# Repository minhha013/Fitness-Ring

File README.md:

# Smart Fitness Ring PCB

This branch contains the PCB design files for the Smart Fitness Ring project, a low-cost wearable device designed to track basic biometrics such as steps, heart rate, and Basal Metabolic Rate (BMR). The purpose of this branch is to document the electrical design and hardware development process behind the custom ring electronics.

The PCB is being developed to support a compact and wearable form factor while integrating the key sensing and processing components needed for health tracking. Because the ring is intended to remain small, lightweight, and practical, the PCB design requires careful consideration of size constraints, component placement, routing, and power management.

## Purpose

The goal of this PCB design is to create a reliable and compact hardware platform that can serve as the foundation for an affordable fitness ring. Many commercial smart rings are expensive and often require subscription fees, which can make health tracking less accessible. This project aims to explore how a custom-designed solution can provide useful biometric tracking at a lower cost.

## PCB Features

- Custom PCB designed in KiCad
- Intended for integration into a compact smart ring
- Supports step tracking functionality
- Supports heart rate sensing
- Supports BMR estimation through collected biometric data
- Designed with wearable size constraints in mind

## Current Status

PCB design in progress.

## Notes

This branch is dedicated specifically to PCB development and hardware design. Other parts of the project, such as CAD modeling, enclosure design, and software/app development, are managed separately.

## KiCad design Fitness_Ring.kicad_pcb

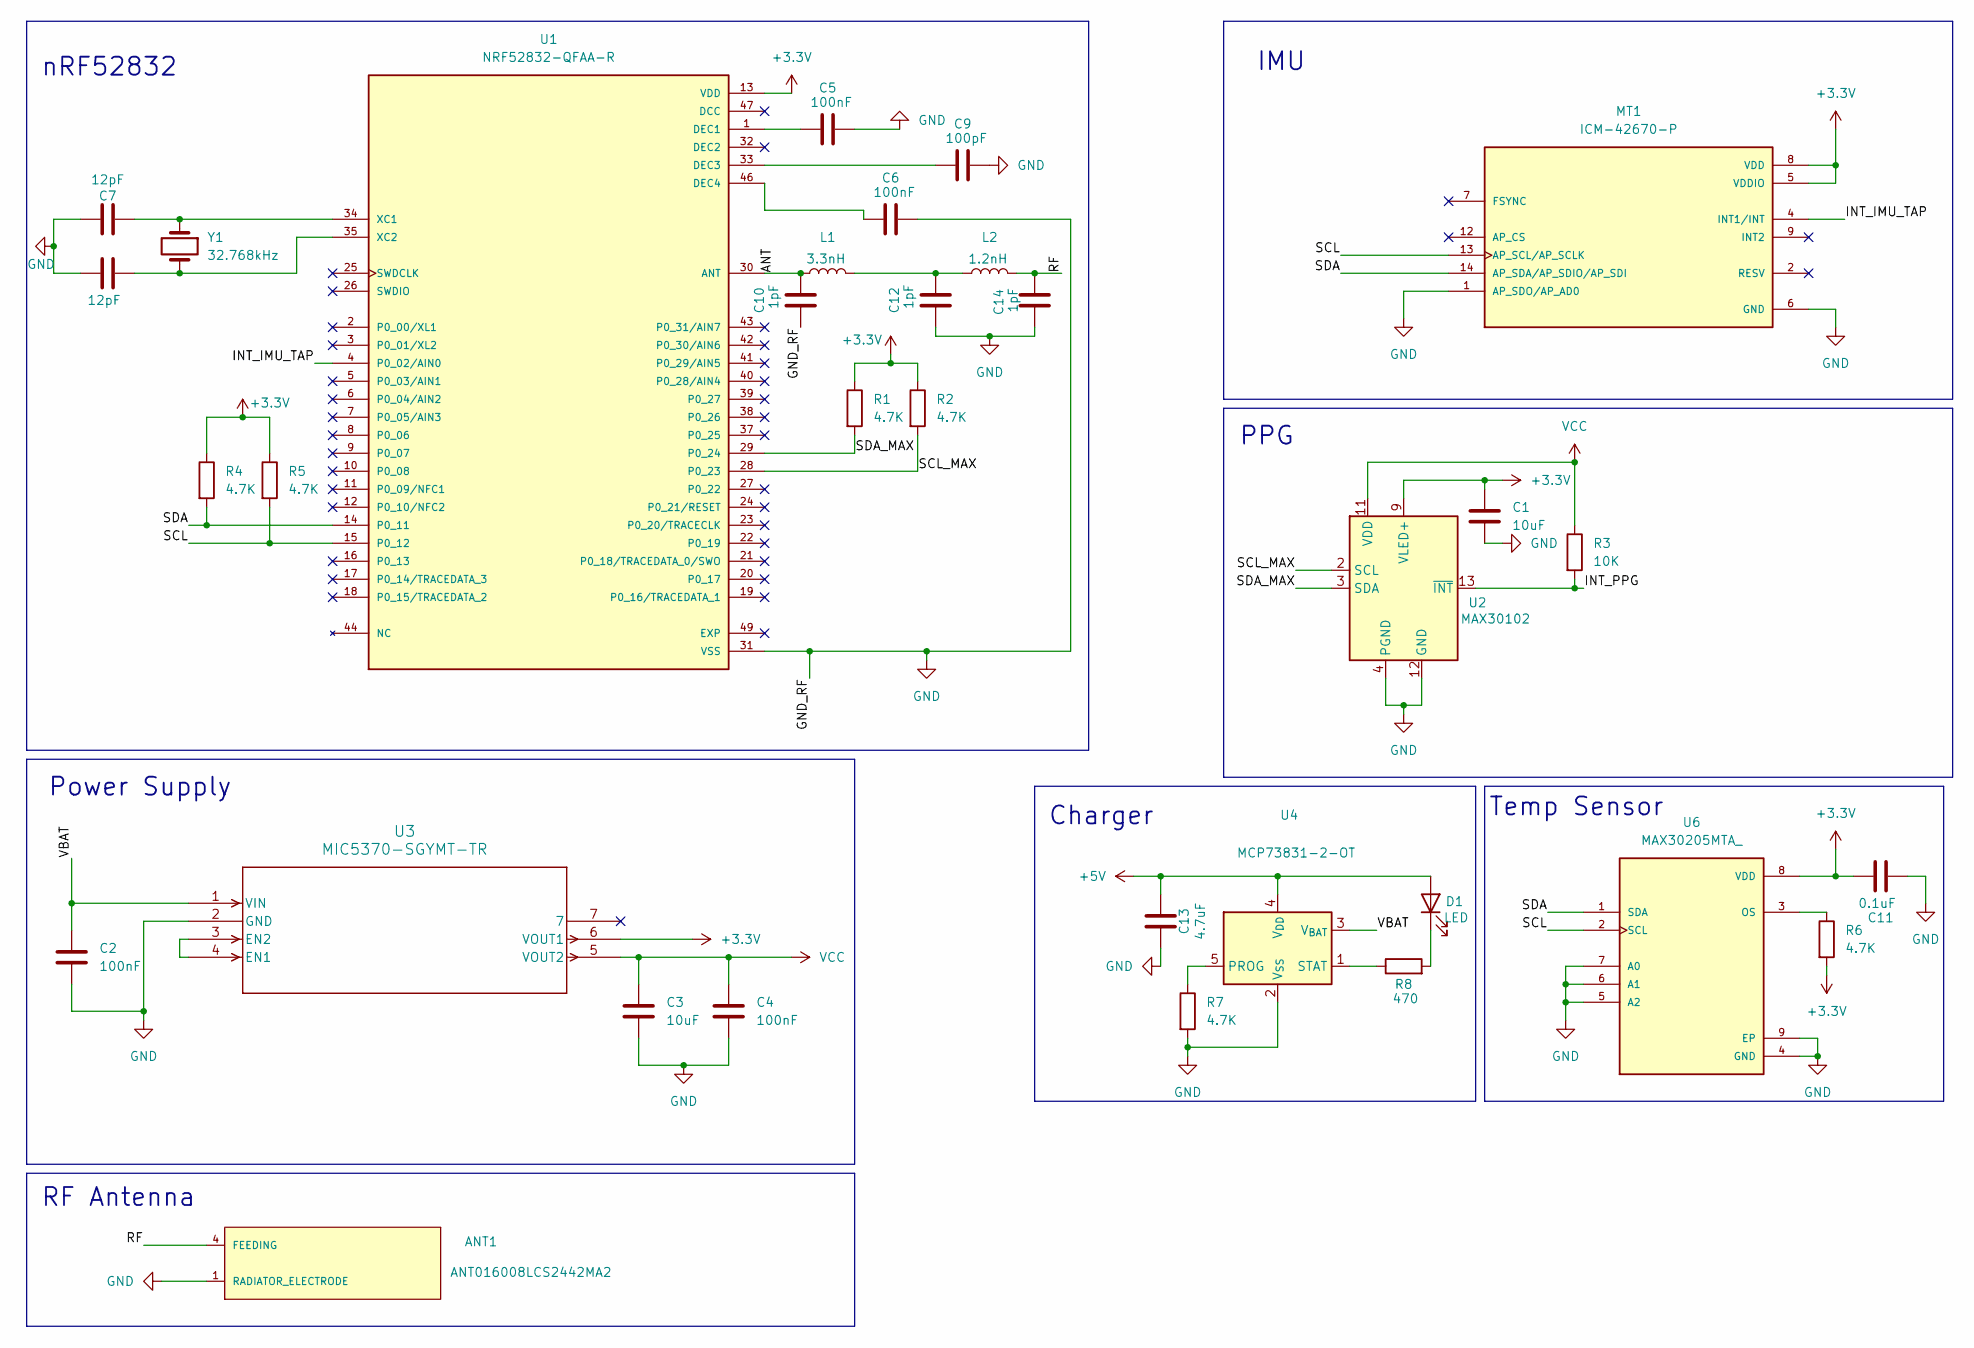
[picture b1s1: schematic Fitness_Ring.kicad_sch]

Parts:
ANT1: ANT016008LCS2442MA2; ANT_ANT016008LCS2442MA2
C1, C3: 10uF; C_0201_0603Metric
C2, C4, C5, C6: 100nF; C_0201_0603Metric
C7, C8: 12pF; C_0201_0603Metric
C9: 100pF; C_0201_0603Metric
C10, C12, C14: 1pF; C_0201_0603Metric
C11: 0.1uF; C_0201_0603Metric
C13: 4.7uF; C_0201_0603Metric
D1: LED; LED_0201_0603Metric
L1: 3.3nH; L_0201_0603Metric
L2: 1.2nH; L_0201_0603Metric
MT1: ICM-42670-P; PARTREV 1.1
R1, R2, R4, R5, R6, R7: 4.7K; R_0201_0603Metric
R3: 10K; R_0201_0603Metric
R8: 470; R_0201_0603Metric
U1: NRF52832-QFAA-R; nRF52832; PARTREV 1.9
U2: MAX30102; Maxim_OLGA-14_3.3x5.6mm_P0.8mm
U3: MIC5370-SGYMT-TR; MIC5370
U4: MCP73831-2-OT; SOT-23-5
U6: MAX30205MTA_; MAX30205
Y1: 32.768kHz; Crystal_SMD_2012-2Pin_2.0x1.2mm

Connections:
+3.3V: C1.1, C11.2, MT1.5 (VDDIO), MT1.8 (VDD), R1.1, R2.1, R4.1, R5.1, R6.2, U1.13 (VDD), U1.36 (VDD), U1.48 (VDD), U2.9 (VLED+), U2.10 (VLED+), U3.6 (VOUT1), U6.8 (VDD)
+5V: C13.2, D1.2 (A), U4.4 (V_{DD})
/ANT: C10.2, L1.1, U1.30 (ANT)
/INT_IMU_TAP: MT1.4 (INT1/INT), U1.4 (P0_02/AIN0)
/INT_PPG: R3.2, U2.13 (~INT)
/RF: ANT1.4 (FEEDING), C14.2, L2.2
/SCL: MT1.13 (AP_SCL/AP_SCLK), R5.2, U1.15 (P0_12), U6.2 (SCL)
/SCL_MAX: R2.2, U1.28 (P0_23), U2.2 (SCL)
/SDA: MT1.14 (AP_SDA/AP_SDIO/AP_SDI), R4.2, U1.14 (P0_11), U6.1 (SDA)
/SDA_MAX: R1.2, U1.29 (P0_24), U2.3 (SDA)
/VBAT: C2.1, U3.1 (VIN), U4.3 (V_{BAT})
GND: ANT1.1 (RADIATOR_ELECTRODE), C1.2, C2.2, C3.2, C4.2, C5.2, C6.2, C7.2, C8.2, C9.2, C10.1, C11.1, C12.1, C13.1, C14.1, MT1.1 (AP_SDO/AP_AD0), MT1.6 (GND), R7.2, U1.31 (VSS), U1.45 (VSS), U2.4 (PGND), U2.12 (GND), U3.2 (GND), U4.2 (V_{SS}), U6.4 (GND), U6.5 (A2), U6.6 (A1), U6.7 (A0), U6.9 (EP)
unnamed: C12.2, L1.2, L2.1
unnamed: D1.1 (K), R8.2
unnamed: C5.1, U1.1 (DEC1)
unnamed: C9.1, U1.33 (DEC3)
unnamed: C6.1, U1.46 (DEC4)
unnamed: C7.1, U1.34 (XC1), Y1.1
unnamed: C8.1, U1.35 (XC2), Y1.2
unnamed: U3.3 (EN2), U3.4 (EN1)
unnamed: R7.1, U4.5 (PROG)
unnamed: R8.1, U4.1 (STAT)
unnamed: R6.1, U6.3 (OS)
VCC: C3.1, C4.1, R3.1, U2.11 (VDD), U3.5 (VOUT2)

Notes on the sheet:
Charger
nRF52832
PPG
RF Antenna
IMU
Temp Sensor
Power Supply

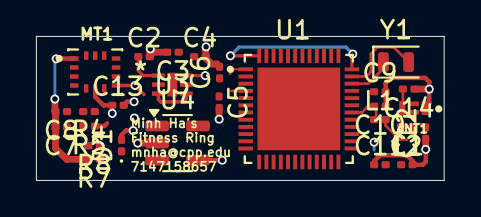
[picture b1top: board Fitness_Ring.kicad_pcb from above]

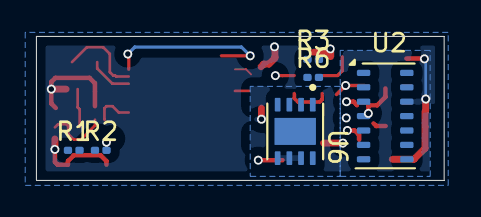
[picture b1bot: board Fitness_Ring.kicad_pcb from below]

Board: 2 copper layers, 22.6 x 8.0 mm, 33 parts (6 on the bottom side), 24 nets.

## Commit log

2026-04-07 Initial Kicad Project Files
2026-04-07 made changes to schematic
2026-04-13 Finalized the schematic
2026-04-13 Finished adding all the footprints and updated the PCB from schematic
2026-04-21 placed all components on the PCB, need to make sure to change schematic so that MAX30102 has its own separate I2C bus
2026-04-22 Removed the level translator as we do not need it anymore, switching to a flex PCB with two layers to fix the trace impedance width problem while not going up too much in cost, will work on that next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
2026-04-22 changed the board to a flex board, added keepout zones and ground pour for bottom layer, need to fix Antenna
2026-04-26 Create Solidworks_Ring
2026-04-26 Prototype_Ring
2026-04-26 Add new Ring file in Solidworks directory
2026-04-26 Add files via upload
    Prototype Fitness Ring Design
2026-04-26 Add files via upload
    Images of the Design of the Ring
2026-04-26 Revise README for Smart Fitness Ring PCB project
    Updated the README to reflect the Smart Fitness Ring project, detailing the PCB design, purpose, features, and current status.
2026-04-29 Fixed RF pi network and began doing traces
2026-04-30 worked on more routing
